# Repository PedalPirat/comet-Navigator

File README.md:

# comet-Navigator
Extension for the [Mecha Comet](https://mecha.so/comet) based on the nRF54H20 with GPS, IMU and CAN

Part of the [PedalPirat](https://github.com/PedalPirat/PedalPirat) ecosystem, intended to be used with the [pizero_bikecomputer](https://github.com/hishizuka/pizero_bikecomputer)

## Motivation
I want to use the pizero_bikecomputer on a Mecha Comet. For it to work it needs some sensors as described [here](https://github.com/hishizuka/pizero_bikecomputer/blob/master/doc/hardware_installation.md), so the goal is to create a PCB with
- Nordic [nRF54H20](https://www.nordicsemi.com/Products/nRF54H20)
  - Supports ANT+ (soon)
  - CAN
  - USB Host to connect to the Comet
- u-blox [MAX-M10S](https://www.u-blox.com/en/product/max-m10-series) (GPS)
- Bosch [BHI385](https://www.bosch-sensortec.com/products/smart-sensor-systems/bhi385/) (IMU/Environmental)
- CAN-Transceiver (to connect to the PedalPirat or E-Bikes)
- 5 Buttons (to control the Software)
- USB Hub (?) to connect AI-Cameras
- Power Delivery to charge the Comet
- GPIO/I2C/SPI Breakout

## Design Idea
### PCB
The core will be a nRF54H20 MCU by Nordic to which the other Components get connected to.

There also needs to be a connector for the GPS antenna or an onboard antenna.

- Green1 = BHI385
- Blue = GPS Antenna
- Red = uBlox MAX-10S
- Green2 = Ezurio BL54H20 (nRF54H20)
- Yellow = CAN Transceiver
- White = BT/ANT+ Antenna

### Firmware
The firmware will be written for the Nordic [nRF Connect SDK](https://docs.nordicsemi.com/bundle/ncs-2.5.2/page/nrf/index.html) which is based on the [Zephyr RTOS](https://github.com/zephyrproject-rtos/zephyr).

The data of the sensors is accessed by the Comet via USB.

### Mounting
#### Comet Extension
Extension that mounts on the Extension Interface of the Comet and screws to it's side to ensure it doesn't move.

[Comet Pin-Out Docs](https://developers.mecha.so/comet/working-with-io/pin-diagram)
#### Mount/Dock
Dock for the Comet that includes an USB-Hub to connect Cameras etc, connects CAN and Power.

Maybe something like the Bosch Intuvia Dock 

[Intuvia-Teardown](https://www.youtube.com/watch?v=ptTAljXuzoo)
[More Teardown](https://www.youtube.com/watch?v=TgO4bjzqhkQ)

### Forum Discussion
[Mecha-org Forum Post](https://forum.mecha.so/t/comet-navigator-extension-with-gps-imu-can-ant/165)

## Existing Products / Designs
- [Comet Gamepad V1](https://github.com/PedalPirat/comet-Navigator/tree/main/resources/mecha/Comet-Gamepad-V1)
- [SparkFun MAX-M10S](https://github.com/sparkfun/SparkFun_u-blox_MAX-M10S)
- [Bosch BHI385 Shuttle board](https://www.bosch-sensortec.com/media/boschsensortec/downloads/shuttle_board_flyer/application_board_3_1/bst-bhi385-sf000-00.pdf)

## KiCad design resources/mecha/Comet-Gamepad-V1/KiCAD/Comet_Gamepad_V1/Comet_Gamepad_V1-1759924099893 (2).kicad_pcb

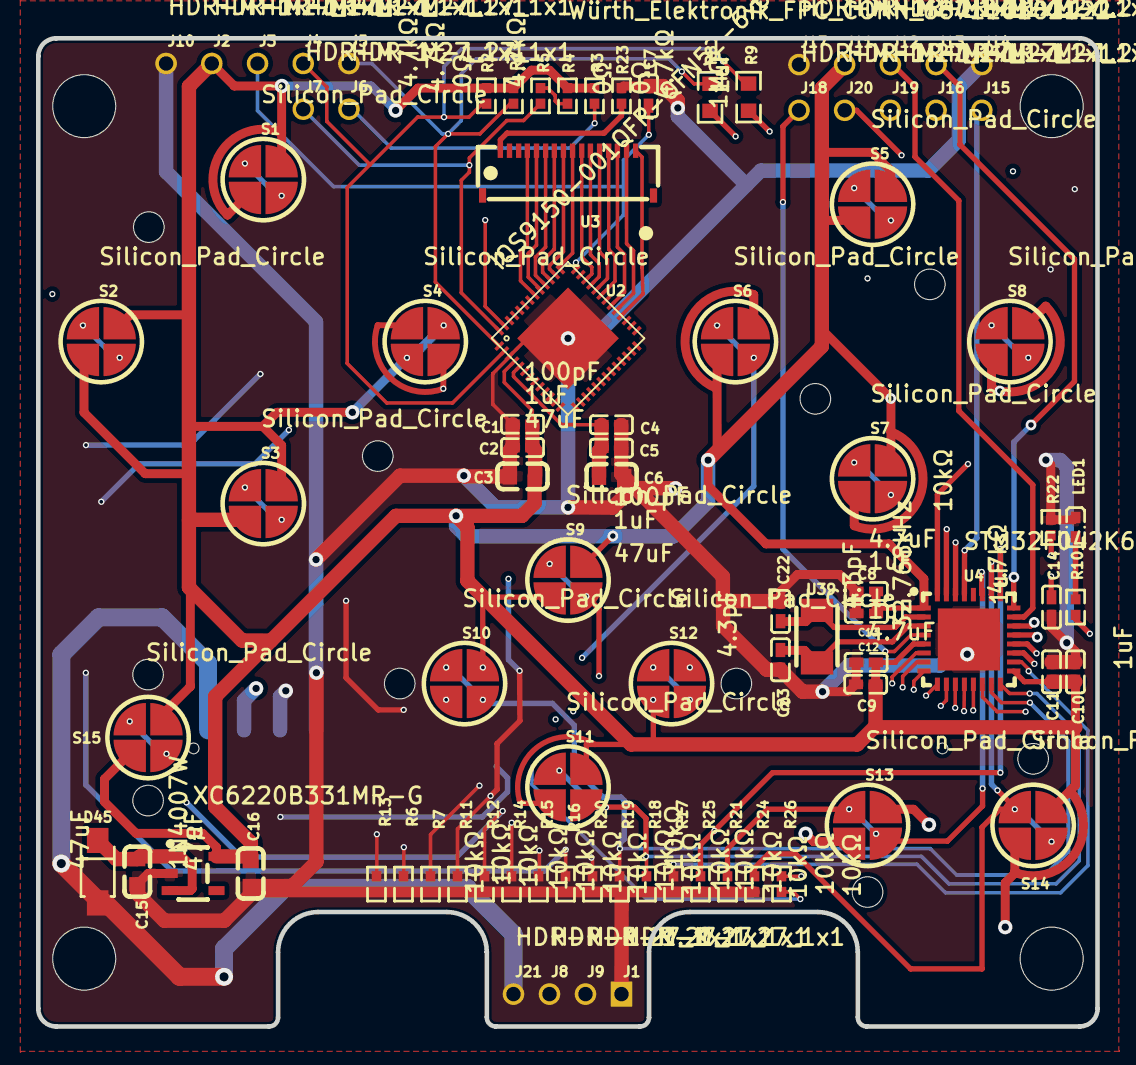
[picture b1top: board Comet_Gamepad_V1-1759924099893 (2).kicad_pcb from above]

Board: 4 copper layers, 58.8 x 54.9 mm, 102 parts (1 on the bottom side), 55 nets.

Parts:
C1, C4: 100pF; C0402
C2, C5, C7, C11, C12, C13, C14: 1uF; C0402
C3, C6, C15, C16: 47uF; C0603
C8, C9, C10: 4.7uF; C0402
C22, C23: 4.3pF; C0402
D45: 1N4007W; SOD-123FL_L2.7-W1.8-LS3.8-RD
Hole_gge8298: Hole_gge8298
Hole_gge8301: Hole_gge8301
Hole_gge8304: Hole_gge8304
Hole_gge8307: Hole_gge8307
Hole_gge45780: Hole_gge45780
Hole_gge45822: Hole_gge45822
Hole_gge45837: Hole_gge45837
Hole_gge45852: Hole_gge45852
Hole_gge45867: Hole_gge45867
Hole_gge45882: Hole_gge45882
Hole_gge45897: Hole_gge45897
Hole_gge45912: Hole_gge45912
Hole_gge46029: Hole_gge46029
Hole_gge46044: Hole_gge46044
J1, J2, J3, J4, J5, J6, J7, J8, J9, J10, J11, J12, J13, J14, J15, J16, J17, J18, J19, J20, J21: HDR-M-1.27_1x1; HDR-M-1.27_1X1
LED1: IN-S42ATUW; LED0402-RD_WHITE
Q1: XC6220B331MR-G; SOT-25_L3.0-W1.6-P0.95-LS2.8-TL
R1, R2, R3, R4, R10: 4.7kΩ; R0402
R5: 0Ω; R0402
R6, R7, R11, R12, R13, R14, R15, R16, R17, R18, R19, R20, R21, R22, R24, R25, R26: 10kΩ; R0402
R8, R9: 0Ω; R0603
R23: 1MΩ; R0402
S1, S2, S3, S4, S5, S6, S7, S8, S9, S10, S11, S12, S13, S14, S15: Silicon_Pad_Circle; SILICON_PAD_CIRCLE
U1: 20X2-POGO-PINS-PADS-2MM-PITCH
U2: IQS9150-001QFR-QFN52-6x6; IQS9150-001QFR-QFN52-6X6
U3: Würth_Elektronik_FPC_CONN_687116182122; WÜRTH_ELEKTRONIK_FPC_CONN_687116182122_CONN-SMD_16P-P0.50
U4: STM32F042K6U6TR; UFQFPN-32_L5.0-W5.0-P0.50-TL-EP3.5
U39: 32.768kHz; CRYSTAL-SMD_L3.2-W1.5

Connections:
3V3: C1.2, C2.2, C3.2, C8.2, C9.2, C10.2, C11.2, C12.2, C13.2, C16.2, J2.1, J11.1, Q1.5, R1.2, R2.2, R3.2, R4.1, R26.2, S1.2, S2.2, S3.2, S4.2, S5.2, S6.2, S7.2, S8.2, S9.2, S10.2, S11.2, S12.2, S13.2, S14.2, S15.2, U2.4, U4.1, U4.5, U4.17
BOOT0_PF11: J17.1, R22.1, U1.19, U4.31
C6_2: C4.2, C5.2, C6.2, U2.5
C15_2: C15.2, D45.1, Q1.1, Q1.3
C22_2: C22.2, U4.2, U39.1
C23_2: C23.2, U4.3, U39.2
GND: C1.1, C2.1, C3.1, C4.1, C5.1, C6.1, C7.1, C8.1, C9.1, C10.1, C11.1, C12.1, C13.1, C14.1, C15.1, C16.1, C22.1, C23.1, J1.1, J10.1, J14.1, LED1.1, Q1.2, R6.2, R7.2, R11.2, R12.2, R13.2, R14.2, R15.2, R16.2, R17.2, R18.2, R19.2, R20.2, R21.2, R22.2, R23.1, R24.2, R25.2, U1.4, U2.3, U2.53, U4.33
J7_1: J7.1, R5.1, U2.52
LED1_2: LED1.2, R10.2
MCLR/VPP: C7.2, J3.1, U2.39
NRST: C14.2, J18.1, U4.4
PA0_L1: R13.1, S1.1, U4.6
PA1_L2: R6.1, S2.1, U4.7
PA2_L3: R7.1, S3.1, U4.8
PA3_L4: R11.1, S4.1, U4.9
PA4_R1: R12.1, S5.1, U4.10
PA5_R2: R14.1, S6.1, U4.11
PA6_R3: R15.1, S7.1, U4.12
PA7_R4: R16.1, S8.1, U4.13
PA8_M4: R17.1, S12.1, U4.18
PA9: J19.1, U4.19
PA10: J20.1, U4.20
PA15: R25.1, S15.1, U4.25
PB0_M1: R20.1, S9.1, U4.14
PB1_M2: R19.1, S10.1, U4.15
PB2_M3: R18.1, S11.1, U4.16
PB3: R24.1, S14.1, U4.26
PB4: R21.1, S13.1, U4.27
PB6_SCL: J15.1, R8.1, U4.29
PB7_SDA: J16.1, R9.1, U4.30
R5_2: R4.2, R5.2
R23_2: R23.2, U3.1
RDY: J6.1, R3.1, U2.51
RX10: U2.31, U3.15
RX11: U2.34, U3.13
RX12: U2.36, U3.11
RX22: U2.30, U3.16
RX23: U2.32, U3.14
RX24: U2.35, U3.12
RX25: U2.37, U3.10
SCL: J5.1, R1.1, R8.2, U2.1
SDA: J4.1, R2.1, R9.2, U2.2
SWCLK: J13.1, U4.24
SWDIO: J12.1, U4.23
TX33: U2.40, U3.9
TX34: U2.41, U3.8
TX35: U2.42, U3.7
TX36: U2.43, U3.6
TX37: U2.44, U3.5
TX38: U2.45, U3.4
U1_20: R26.1, U1.20
U4_32: R10.1, U4.32
USB_DM: J8.1, U1.2, U4.21
USB_DP: J9.1, U1.3, U4.22
VDD_5V: D45.2, J21.1, U1.1

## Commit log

2025-10-23 updated readme, added files and datasheets
2025-10-23 added KiCAD File of Gamepad
2025-10-23 restructure
2025-10-23 added comet mechanical files, continuted readme
2025-10-23 updated files, readme
2025-10-23 updated files
2025-10-24 files
2025-10-26 added bosch mount
2025-10-26 updated readme, added photo of PCB / Mounting sketch
2025-10-26 updated readme and mount
2025-10-28 added stuff?
